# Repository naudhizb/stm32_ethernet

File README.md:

# stm32_ethernet
side project making stm32 ethernet module

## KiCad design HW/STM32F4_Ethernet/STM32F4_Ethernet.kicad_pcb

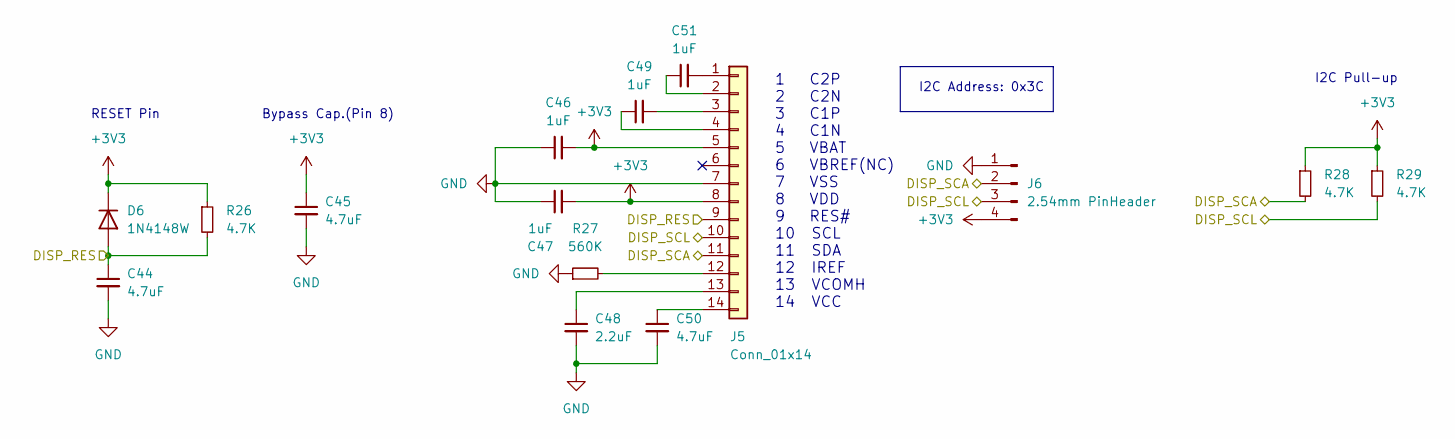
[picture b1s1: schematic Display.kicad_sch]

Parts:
C44, C45, C50: 4.7uF; C_0603_1608Metric_Pad1.08x0.95mm_HandSolder
C46, C47, C49, C51: 1uF; C_0603_1608Metric_Pad1.08x0.95mm_HandSolder
C48: 2.2uF; C_0603_1608Metric_Pad1.08x0.95mm_HandSolder
D6: 1N4148W; D_SOD-123
J5: Conn_01x14; OLED0_49
J6: 2.54mm PinHeader; PinHeader_1x04_P2.54mm_Vertical
R26, R28, R29: 4.7K; R_0603_1608Metric_Pad0.98x0.95mm_HandSolder
R27: 560K; R_0603_1608Metric_Pad0.98x0.95mm_HandSolder

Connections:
+3V3: C45.1, C46.2, C47.2, D6.1 (K), J5.5, J5.8, J6.4, R26.1, R28.1, R29.1; also elsewhere on the board
/Display/DISP_RES: C44.1, D6.2 (A), J5.9, R26.2
/Display/DISP_SCA: J5.11, J6.2, R28.2; also elsewhere on the board
/Display/DISP_SCL: J5.10, J6.3, R29.2; also elsewhere on the board
GND: C44.2, C45.2, C46.1, C47.1, C48.2, C50.2, J5.7, J6.1, R27.1; also elsewhere on the board
unnamed: C48.1, J5.13
unnamed: C49.1, J5.4
unnamed: C49.2, J5.3
unnamed: C50.1, J5.14
unnamed: C51.1, J5.2
unnamed: C51.2, J5.1
unnamed: J5.12, R27.2

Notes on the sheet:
1 C2P 2 C2N 3 C1P 4 C1N 5 VBAT 6 VBREF(NC) 7 VSS 8 VDD 9 RES# 10 SCL 11 SDA 12 IREF 13 VCOMH 14 VCC
I2C Pull-up
I2C Address: 0x3C
RESET Pin
Bypass Cap.(Pin 8)

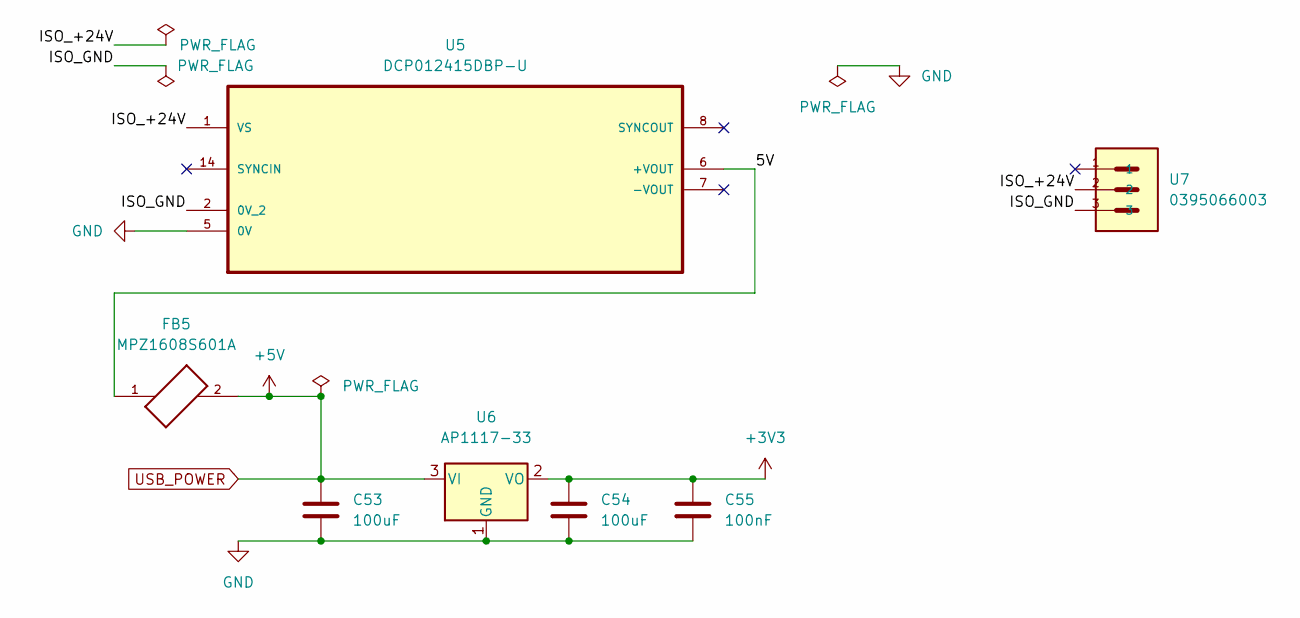
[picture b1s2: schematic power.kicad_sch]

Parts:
C53, C54: 100uF; C_0603_1608Metric_Pad1.08x0.95mm_HandSolder
C55: 100nF; C_0603_1608Metric_Pad1.08x0.95mm_HandSolder
FB5: MPZ1608S601A; BEADC1608X95N
U5: DCP012415DBP-U; SOP254P1050X533-14N; MPN DCP012415DBP-U
U6: AP1117-33; SOT-223-3_TabPin2
U7: 0395066003; MOLEX_0395066003

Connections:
+3V3: C54.1, C55.1, U6.2 (VO); also elsewhere on the board
/Power/5V: FB5.1, U5.6 (+VOUT)
/Power/ISO_+24V: U5.1 (VS), U7.2
/Power/ISO_GND: U5.2 (0V_2), U7.3
GND: C53.2, C54.2, C55.2, U5.5 (0V), U6.1 (GND); also elsewhere on the board
USB_POWER: C53.1, FB5.2, U6.3 (VI); also elsewhere on the board

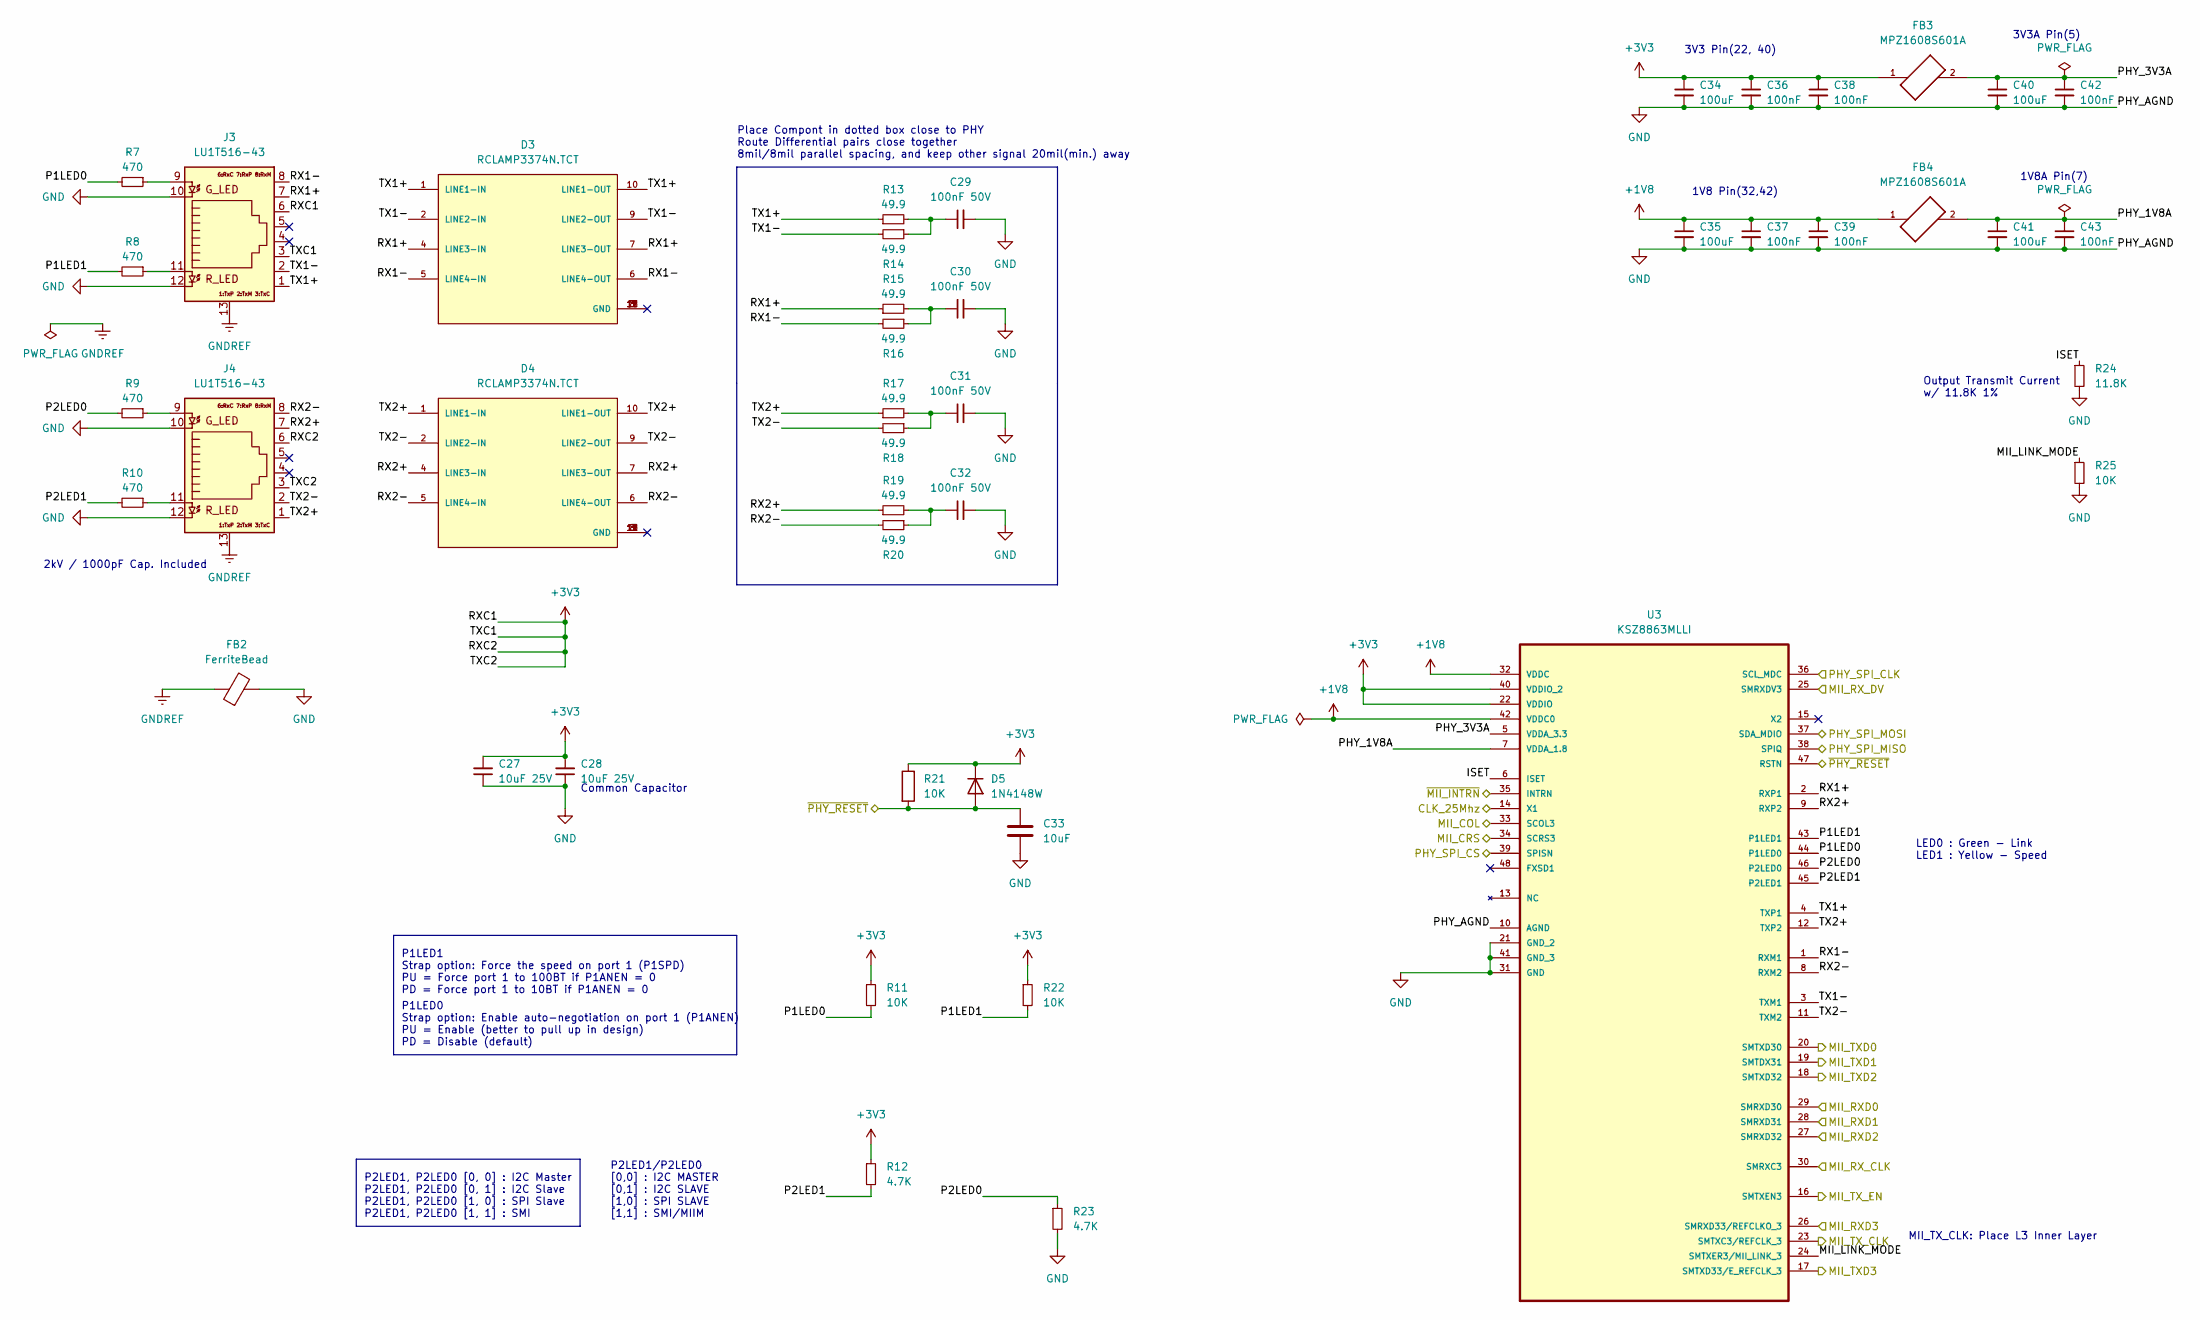
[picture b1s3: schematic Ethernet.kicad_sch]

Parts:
C27, C28: 10uF 25V; C_0603_1608Metric_Pad1.08x0.95mm_HandSolder
C29, C30, C31, C32: 100nF 50V; C_0603_1608Metric_Pad1.08x0.95mm_HandSolder
C33: 10uF; C_0603_1608Metric_Pad1.08x0.95mm_HandSolder
C34, C35, C40, C41: 100uF; C_0603_1608Metric_Pad1.08x0.95mm_HandSolder
C36, C37, C38, C39, C42, C43: 100nF; C_0603_1608Metric_Pad1.08x0.95mm_HandSolder
D3, D4: RCLAMP3374N.TCT; DIODE_RCLAMP3374N.TCT; PARTREV 7/24/2012
D5: 1N4148W; D_SOD-123
FB2: FerriteBead; BEADC1608X95N
FB3, FB4: MPZ1608S601A; BEADC1608X95N
J3, J4: LU1T516-43; LU1T516-43LF
R7, R8, R9, R10: 470; R_0603_1608Metric_Pad0.98x0.95mm_HandSolder
R11, R21, R22, R25: 10K; R_0603_1608Metric_Pad0.98x0.95mm_HandSolder
R12, R23: 4.7K; R_0603_1608Metric_Pad0.98x0.95mm_HandSolder
R13, R14, R15, R16, R17, R18, R19, R20: 49.9; R_0603_1608Metric_Pad0.98x0.95mm_HandSolder
R24: 11.8K; R_0603_1608Metric_Pad0.98x0.95mm_HandSolder
U3: KSZ8863MLLI; QFP50P900X900X160-48N; MPN KSZ8863MLLI

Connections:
+1V8: C35.1, C37.1, C39.1, FB4.1, U3.32 (VDDC), U3.42 (VDDC0)
+3V3: C27.2, C28.2, C34.1, C36.1, C38.1, D5.1 (K), FB3.1, J3.3, J3.6, J4.3, J4.6, R11.1, R12.1, R21.1, R22.1, U3.22 (VDDIO), U3.40 (VDDIO_2); also elsewhere on the board
/Ethernet/ISET: R24.1, U3.6 (ISET)
/Ethernet/MII_LINK_MODE: R25.1, U3.24 (SMTXER3/MII_LINK_3)
/Ethernet/P1LED0: R7.2, R11.2, U3.44 (P1LED0)
/Ethernet/P1LED1: R8.2, R22.2, U3.43 (P1LED1)
/Ethernet/P2LED0: R9.2, R23.1, U3.46 (P2LED0)
/Ethernet/P2LED1: R10.2, R12.2, U3.45 (P2LED1)
/Ethernet/PHY_1V8A: C41.1, C43.1, FB4.2, U3.7 (VDDA_1.8)
/Ethernet/PHY_3V3A: C40.1, C42.1, FB3.2, U3.5 (VDDA_3.3)
/Ethernet/RX1+: D3.4 (LINE3-IN), D3.7 (LINE3-OUT), J3.7, R15.1, U3.2 (RXP1)
/Ethernet/RX1-: D3.5 (LINE4-IN), D3.6 (LINE4-OUT), J3.8, R16.2, U3.1 (RXM1)
/Ethernet/RX2+: D4.4 (LINE3-IN), D4.7 (LINE3-OUT), J4.7, R19.1, U3.9 (RXP2)
/Ethernet/RX2-: D4.5 (LINE4-IN), D4.6 (LINE4-OUT), J4.8, R20.2, U3.8 (RXM2)
/Ethernet/TX1+: D3.1 (LINE1-IN), D3.10 (LINE1-OUT), J3.1, R13.1, U3.4 (TXP1)
/Ethernet/TX1-: D3.2 (LINE2-IN), D3.9 (LINE2-OUT), J3.2, R14.2, U3.3 (TXM1)
/Ethernet/TX2+: D4.1 (LINE1-IN), D4.10 (LINE1-OUT), J4.1, R17.1, U3.12 (TXP2)
/Ethernet/TX2-: D4.2 (LINE2-IN), D4.9 (LINE2-OUT), J4.2, R18.2, U3.11 (TXM2)
/MCU/ETH_COL: U3.33 (SCOL3); also elsewhere on the board
/MCU/ETH_CRS: U3.34 (SCRS3); also elsewhere on the board
/MCU/ETH_INT: U3.35 (INTRN); also elsewhere on the board
/MCU/ETH_RESET: C33.1, D5.2 (A), R21.2, U3.47 (RSTN); also elsewhere on the board
/MCU/ETH_RXD0: U3.29 (SMRXD30); also elsewhere on the board
/MCU/ETH_RXD1: U3.28 (SMRXD31); also elsewhere on the board
/MCU/ETH_RXD2: U3.27 (SMRXD32); also elsewhere on the board
/MCU/ETH_RXD3: U3.26 (SMRXD33/REFCLKO_3); also elsewhere on the board
/MCU/ETH_RX_CLK: U3.30 (SMRXC3); also elsewhere on the board
/MCU/ETH_RX_DV: U3.25 (SMRXDV3); also elsewhere on the board
/MCU/ETH_TXD0: U3.20 (SMTXD30); also elsewhere on the board
/MCU/ETH_TXD1: U3.19 (SMTDX31); also elsewhere on the board
/MCU/ETH_TXD2: U3.18 (SMTXD32); also elsewhere on the board
/MCU/ETH_TXD3: U3.17 (SMTXD33/E_REFCLK_3); also elsewhere on the board
/MCU/ETH_TX_CLK: U3.23 (SMTXC3/REFCLK_3); also elsewhere on the board
/MCU/ETH_TX_EN: U3.16 (SMTXEN3); also elsewhere on the board
/MCU/MCO_25MHz: U3.14 (X1); also elsewhere on the board
/MCU/SPI_MISO: U3.38 (SPIQ); also elsewhere on the board
/MCU/SPI_MOSI: U3.37 (SDA_MDIO); also elsewhere on the board
/MCU/SPI_NSS: U3.39 (SPISN); also elsewhere on the board
/MCU/SPI_SCK: U3.36 (SCL_MDC); also elsewhere on the board
GND: C27.1, C28.1, C29.2, C30.2, C31.2, C32.2, C33.2, C34.2, C35.2, C36.2, C37.2, C38.2, C39.2, C40.2, C41.2, C42.2, C43.2, FB2.2, J3.10, J3.12, J4.10, J4.12, R23.2, R24.2, R25.2, U3.10 (AGND), U3.21 (GND_2), U3.31 (GND), U3.41 (GND_3); also elsewhere on the board
GNDREF: FB2.1, J3.13, J4.13
unnamed: C29.1, R13.2, R14.1
unnamed: C30.1, R15.2, R16.1
unnamed: C31.1, R17.2, R18.1
unnamed: C32.1, R19.2, R20.1
unnamed: J3.9, R7.1
unnamed: J3.11, R8.1
unnamed: J4.9, R9.1
unnamed: J4.11, R10.1

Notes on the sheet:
P1LED1 Strap option: Force the speed on port 1 (P1SPD) PU = Force port 1 to 100BT if P1ANEN = 0 PD = Force port 1 to 10BT if P1ANEN = 0
1V8A Pin(7)
Output Transmit Current w/ 11.8K 1%
1V8 Pin(32,42)
Place Compont in dotted box close to PHY Route Differential pairs close together 8mil/8mil parallel spacing, and keep other signal 20mil(min.) away
P2LED1, P2LED0 [0, 0] : I2C Master P2LED1, P2LED0 [0, 1] : I2C Slave P2LED1, P2LED0 [1, 0] : SPI Slave P2LED1, P2LED0 [1, 1] : SMI
P1LED0 Strap option: Enable auto-negotiation on port 1 (P1ANEN) PU = Enable (better to pull up in design) PD = Disable (default)
MII_TX_CLK: Place L3 Inner Layer
Common Capacitor
3V3 Pin(22, 40)
2kV / 1000pF Cap. Included
LED0 : Green - Link LED1 : Yellow - Speed
3V3A Pin(5)
P2LED1/P2LED0 [0,0] : I2C MASTER [0,1] : I2C SLAVE [1,0] : SPI SLAVE [1,1] : SMI/MIIM

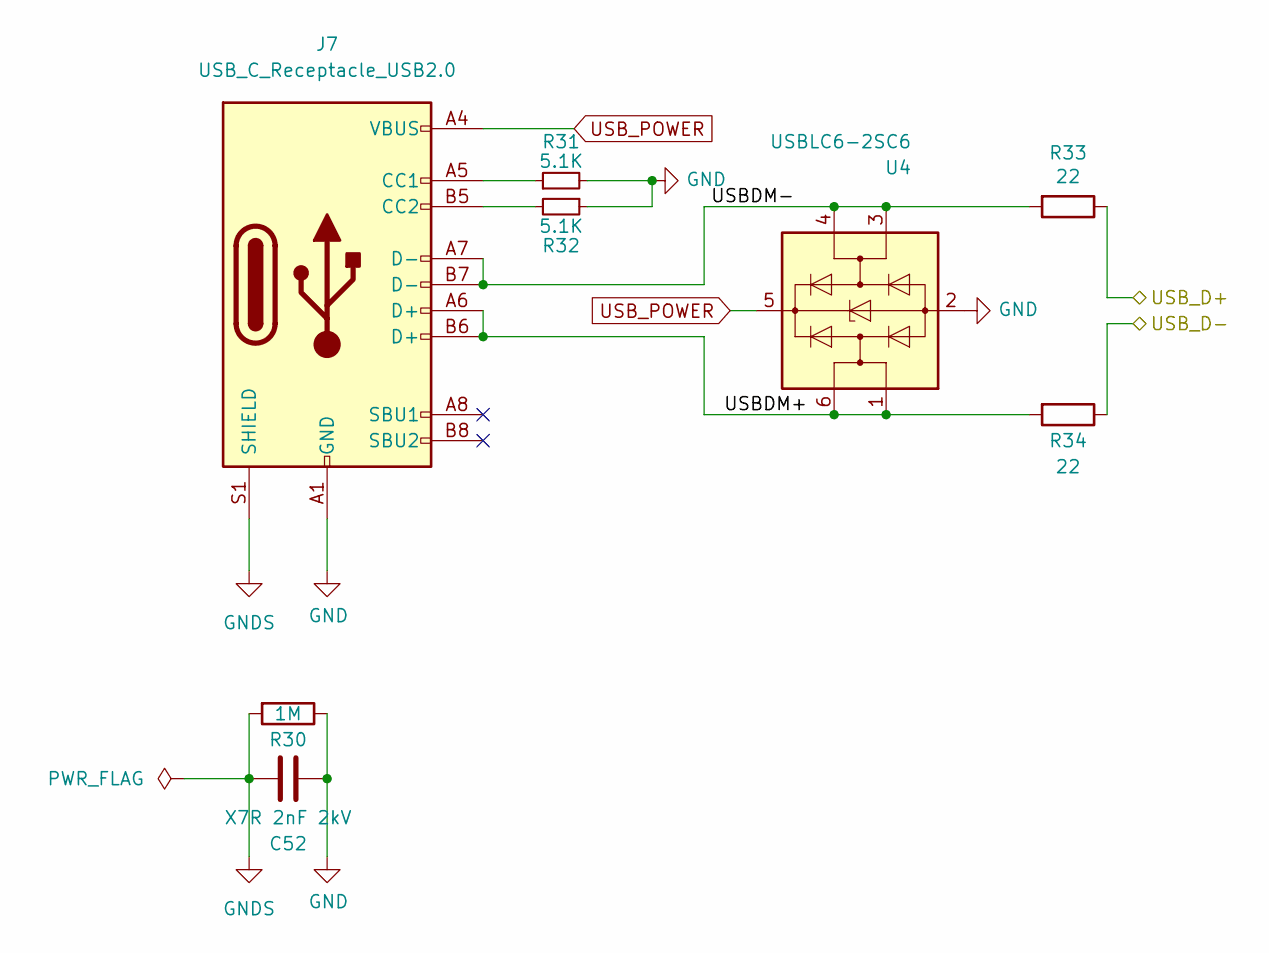
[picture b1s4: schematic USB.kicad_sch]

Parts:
C52: X7R 2nF 2kV; C_0603_1608Metric_Pad1.08x0.95mm_HandSolder
J7: USB_C_Receptacle_USB2.0; USB_C_Receptacle_Palconn_UTC16-G
R30: 1M; R_0603_1608Metric_Pad0.98x0.95mm_HandSolder
R31, R32: 5.1K; R_0603_1608Metric_Pad0.98x0.95mm_HandSolder
R33, R34: 22; R_0603_1608Metric_Pad0.98x0.95mm_HandSolder
U4: USBLC6-2SC6; SOT-23-6

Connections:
/MCU/USB_D+: R33.1; also elsewhere on the board
/MCU/USB_D-: R34.1; also elsewhere on the board
/USB/USBDM+: J7.A6 (D+), J7.B6 (D+), R34.2, U4.1 (I/O1), U4.6 (I/O1)
/USB/USBDM-: J7.A7 (D-), J7.B7 (D-), R33.2, U4.3 (I/O2), U4.4 (I/O2)
GND: C52.1, J7.A1 (GND), J7.A12 (GND), J7.B1 (GND), J7.B12 (GND), R30.1, R31.2, R32.1, U4.2 (GND); also elsewhere on the board
GNDS: C52.2, J7.S1 (SHIELD), R30.2
unnamed: J7.A5 (CC1), R31.1
unnamed: J7.B5 (CC2), R32.2
USB_POWER: J7.A4 (VBUS), J7.A9 (VBUS), J7.B4 (VBUS), J7.B9 (VBUS), U4.5 (VBUS); also elsewhere on the board

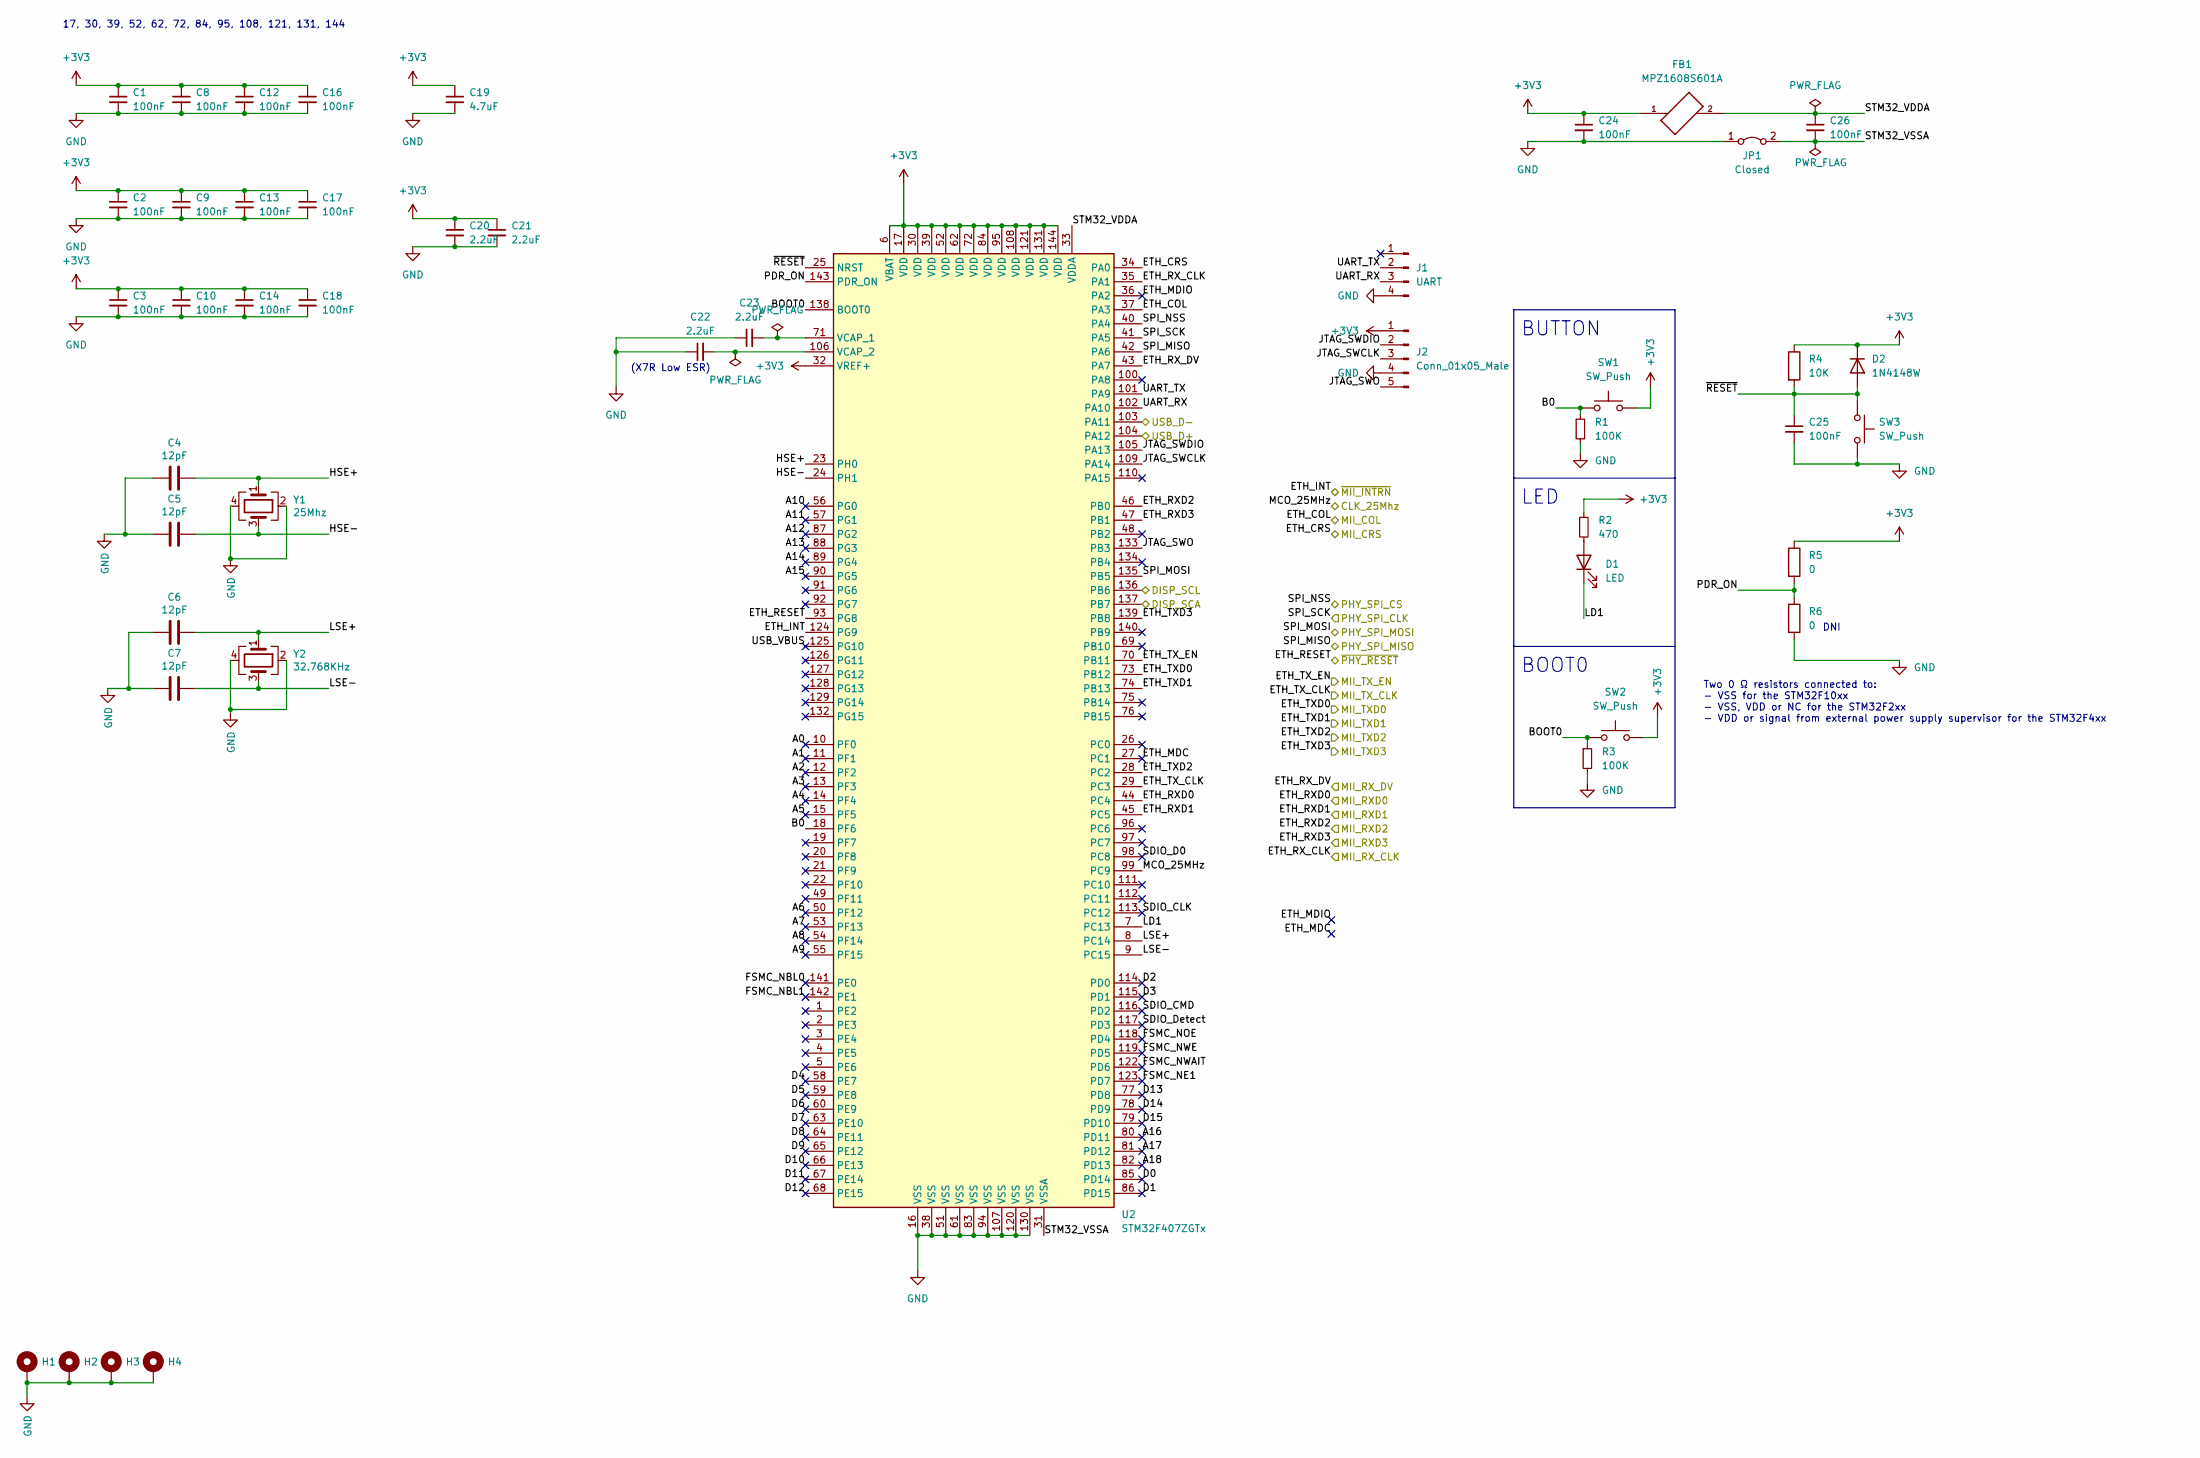
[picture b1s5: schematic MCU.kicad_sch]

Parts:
C1, C2, C3, C8, C9, C10, C12, C13, C14, C16, C17, C18, C24, C25, C26: 100nF; C_0603_1608Metric_Pad1.08x0.95mm_HandSolder
C4, C5, C6, C7: 12pF; C_0603_1608Metric_Pad1.08x0.95mm_HandSolder
C19: 4.7uF; C_0805_2012Metric_Pad1.18x1.45mm_HandSolder
C20, C21, C22, C23: 2.2uF; C_0805_2012Metric_Pad1.18x1.45mm_HandSolder
D1: LED; LED_0603_1608Metric_Pad1.05x0.95mm_HandSolder
D2: 1N4148W; D_SOD-123
FB1: MPZ1608S601A; BEADC1608X95N
H1, H2, H3, H4: MountingHole_3.2mm_M3_ISO7380_Pad
J1: UART; PinHeader_1x04_P2.54mm_Vertical
J2: Conn_01x05_Male; PinHeader_1x05_P2.54mm_Vertical
JP1: Closed; SolderJumper-2_P1.3mm_Open_TrianglePad1.0x1.5mm
R1, R3: 100K; R_0603_1608Metric_Pad0.98x0.95mm_HandSolder
R2: 470; R_0603_1608Metric_Pad0.98x0.95mm_HandSolder
R4: 10K; R_0603_1608Metric_Pad0.98x0.95mm_HandSolder
R5, R6: 0; R_0603_1608Metric_Pad0.98x0.95mm_HandSolder
SW1, SW2, SW3: SW_Push; SW_SPST_B3U-1000P-B
U2: STM32F407ZGTx; LQFP-144_20x20mm_P0.5mm
Y1: 25Mhz; Crystal_SMD_3225-4Pin_3.2x2.5mm_HandSoldering
Y2: 32.768KHz; Crystal_SMD_3225-4Pin_3.2x2.5mm_HandSoldering

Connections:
+3V3: C1.1, C2.1, C3.1, C8.1, C9.1, C10.1, C12.1, C13.1, C14.1, C16.1, C17.1, C18.1, C19.1, C20.1, C21.1, C24.1, D2.1 (K), FB1.1, J2.1, R2.1, R4.1, R5.1, SW1.2, SW2.2, U2.6 (VBAT), U2.17 (VDD), U2.30 (VDD), U2.32 (VREF+), U2.39 (VDD), U2.52 (VDD), U2.62 (VDD), U2.72 (VDD), U2.84 (VDD), U2.95 (VDD), U2.108 (VDD), U2.121 (VDD), U2.131 (VDD), U2.144 (VDD); also elsewhere on the board
/Display/DISP_SCA: U2.137 (PB7); also elsewhere on the board
/Display/DISP_SCL: U2.136 (PB6); also elsewhere on the board
/MCU/A0: U2.10 (PF0)
/MCU/A1: U2.11 (PF1)
/MCU/A2: U2.12 (PF2)
/MCU/A3: U2.13 (PF3)
/MCU/A4: U2.14 (PF4)
/MCU/A5: U2.15 (PF5)
/MCU/A6: U2.50 (PF12)
/MCU/A7: U2.53 (PF13)
/MCU/A8: U2.54 (PF14)
/MCU/A9: U2.55 (PF15)
/MCU/A10: U2.56 (PG0)
/MCU/A11: U2.57 (PG1)
/MCU/A12: U2.87 (PG2)
/MCU/A13: U2.88 (PG3)
/MCU/A14: U2.89 (PG4)
/MCU/A15: U2.90 (PG5)
/MCU/A16: U2.80 (PD11)
/MCU/A17: U2.81 (PD12)
/MCU/A18: U2.82 (PD13)
/MCU/B0: R1.1, SW1.1, U2.18 (PF6)
/MCU/BOOT0: R3.1, SW2.1, U2.138 (BOOT0)
/MCU/D0: U2.85 (PD14)
/MCU/D1: U2.86 (PD15)
/MCU/D2: U2.114 (PD0)
/MCU/D3: U2.115 (PD1)
/MCU/D4: U2.58 (PE7)
/MCU/D5: U2.59 (PE8)
/MCU/D6: U2.60 (PE9)
/MCU/D7: U2.63 (PE10)
/MCU/D8: U2.64 (PE11)
/MCU/D9: U2.65 (PE12)
/MCU/D10: U2.66 (PE13)
/MCU/D11: U2.67 (PE14)
/MCU/D12: U2.68 (PE15)
/MCU/D13: U2.77 (PD8)
/MCU/D14: U2.78 (PD9)
/MCU/D15: U2.79 (PD10)
/MCU/ETH_COL: U2.37 (PA3); also elsewhere on the board
/MCU/ETH_CRS: U2.34 (PA0); also elsewhere on the board
/MCU/ETH_INT: U2.124 (PG9); also elsewhere on the board
/MCU/ETH_MDC: U2.27 (PC1)
/MCU/ETH_MDIO: U2.36 (PA2)
/MCU/ETH_RESET: U2.93 (PG8); also elsewhere on the board
/MCU/ETH_RXD0: U2.44 (PC4); also elsewhere on the board
/MCU/ETH_RXD1: U2.45 (PC5); also elsewhere on the board
/MCU/ETH_RXD2: U2.46 (PB0); also elsewhere on the board
/MCU/ETH_RXD3: U2.47 (PB1); also elsewhere on the board
/MCU/ETH_RX_CLK: U2.35 (PA1); also elsewhere on the board
/MCU/ETH_RX_DV: U2.43 (PA7); also elsewhere on the board
/MCU/ETH_TXD0: U2.73 (PB12); also elsewhere on the board
/MCU/ETH_TXD1: U2.74 (PB13); also elsewhere on the board
/MCU/ETH_TXD2: U2.28 (PC2); also elsewhere on the board
/MCU/ETH_TXD3: U2.139 (PB8); also elsewhere on the board
/MCU/ETH_TX_CLK: U2.29 (PC3); also elsewhere on the board
/MCU/ETH_TX_EN: U2.70 (PB11); also elsewhere on the board
/MCU/FSMC_NBL0: U2.141 (PE0)
/MCU/FSMC_NBL1: U2.142 (PE1)
/MCU/FSMC_NE1: U2.123 (PD7)
/MCU/FSMC_NOE: U2.118 (PD4)
/MCU/FSMC_NWAIT: U2.122 (PD6)
/MCU/FSMC_NWE: U2.119 (PD5)
/MCU/HSE+: C4.1, U2.23 (PH0), Y1.1
/MCU/HSE-: C5.1, U2.24 (PH1), Y1.3
/MCU/JTAG_SWCLK: J2.3, U2.109 (PA14)
/MCU/JTAG_SWDIO: J2.2, U2.105 (PA13)
/MCU/JTAG_SWO: J2.5, U2.133 (PB3)
/MCU/LD1: D1.1 (K), U2.7 (PC13)
/MCU/LSE+: C6.1, U2.8 (PC14), Y2.1
/MCU/LSE-: C7.1, U2.9 (PC15), Y2.3
/MCU/MCO_25MHz: U2.99 (PC9); also elsewhere on the board
/MCU/PDR_ON: R5.2, R6.1, U2.143 (PDR_ON)
/MCU/SDIO_CLK: U2.113 (PC12)
/MCU/SDIO_CMD: U2.116 (PD2)
/MCU/SDIO_D0: U2.98 (PC8)
/MCU/SDIO_Detect: U2.117 (PD3)
/MCU/SPI_MISO: U2.42 (PA6); also elsewhere on the board
/MCU/SPI_MOSI: U2.135 (PB5); also elsewhere on the board
/MCU/SPI_NSS: U2.40 (PA4); also elsewhere on the board
/MCU/SPI_SCK: U2.41 (PA5); also elsewhere on the board
/MCU/STM32_VDDA: C26.1, FB1.2, U2.33 (VDDA)
/MCU/STM32_VSSA: C26.2, JP1.2 (B), U2.31 (VSSA)
/MCU/UART_RX: J1.3, U2.102 (PA10)
/MCU/UART_TX: J1.2, U2.101 (PA9)
/MCU/USB_D+: U2.104 (PA12); also elsewhere on the board
/MCU/USB_D-: U2.103 (PA11); also elsewhere on the board
/MCU/USB_VBUS: U2.125 (PG10)
/MCU/~RESET: C25.1, D2.2 (A), R4.2, SW3.1, U2.25 (NRST)
GND: C1.2, C2.2, C3.2, C4.2, C5.2, C6.2, C7.2, C8.2, C9.2, C10.2, C12.2, C13.2, C14.2, C16.2, C17.2, C18.2, C19.2, C20.2, C21.2, C22.1, C23.1, C24.2, C25.2, H1.1, H2.1, H3.1, H4.1, J1.4, J2.4, JP1.1 (A), R1.2, R3.2, R6.2, SW3.2, U2.16 (VSS), U2.38 (VSS), U2.51 (VSS), U2.61 (VSS), U2.83 (VSS), U2.94 (VSS), U2.107 (VSS), U2.120 (VSS), U2.130 (VSS), Y1.2, Y1.4, Y2.2, Y2.4; also elsewhere on the board
unnamed: C22.2, U2.106 (VCAP_2)
unnamed: C23.2, U2.71 (VCAP_1)
unnamed: D1.2 (A), R2.2

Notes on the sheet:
BUTTON
LED
DNI
BOOT0
17, 30, 39, 52, 62, 72, 84, 95, 108, 121, 131, 144
(X7R Low ESR)
Two 0 Ω resistors connected to: - VSS for the STM32F10xx - VSS, VDD or NC for the STM32F2xx - VDD or signal from external power supply supervisor for the STM32F4xx

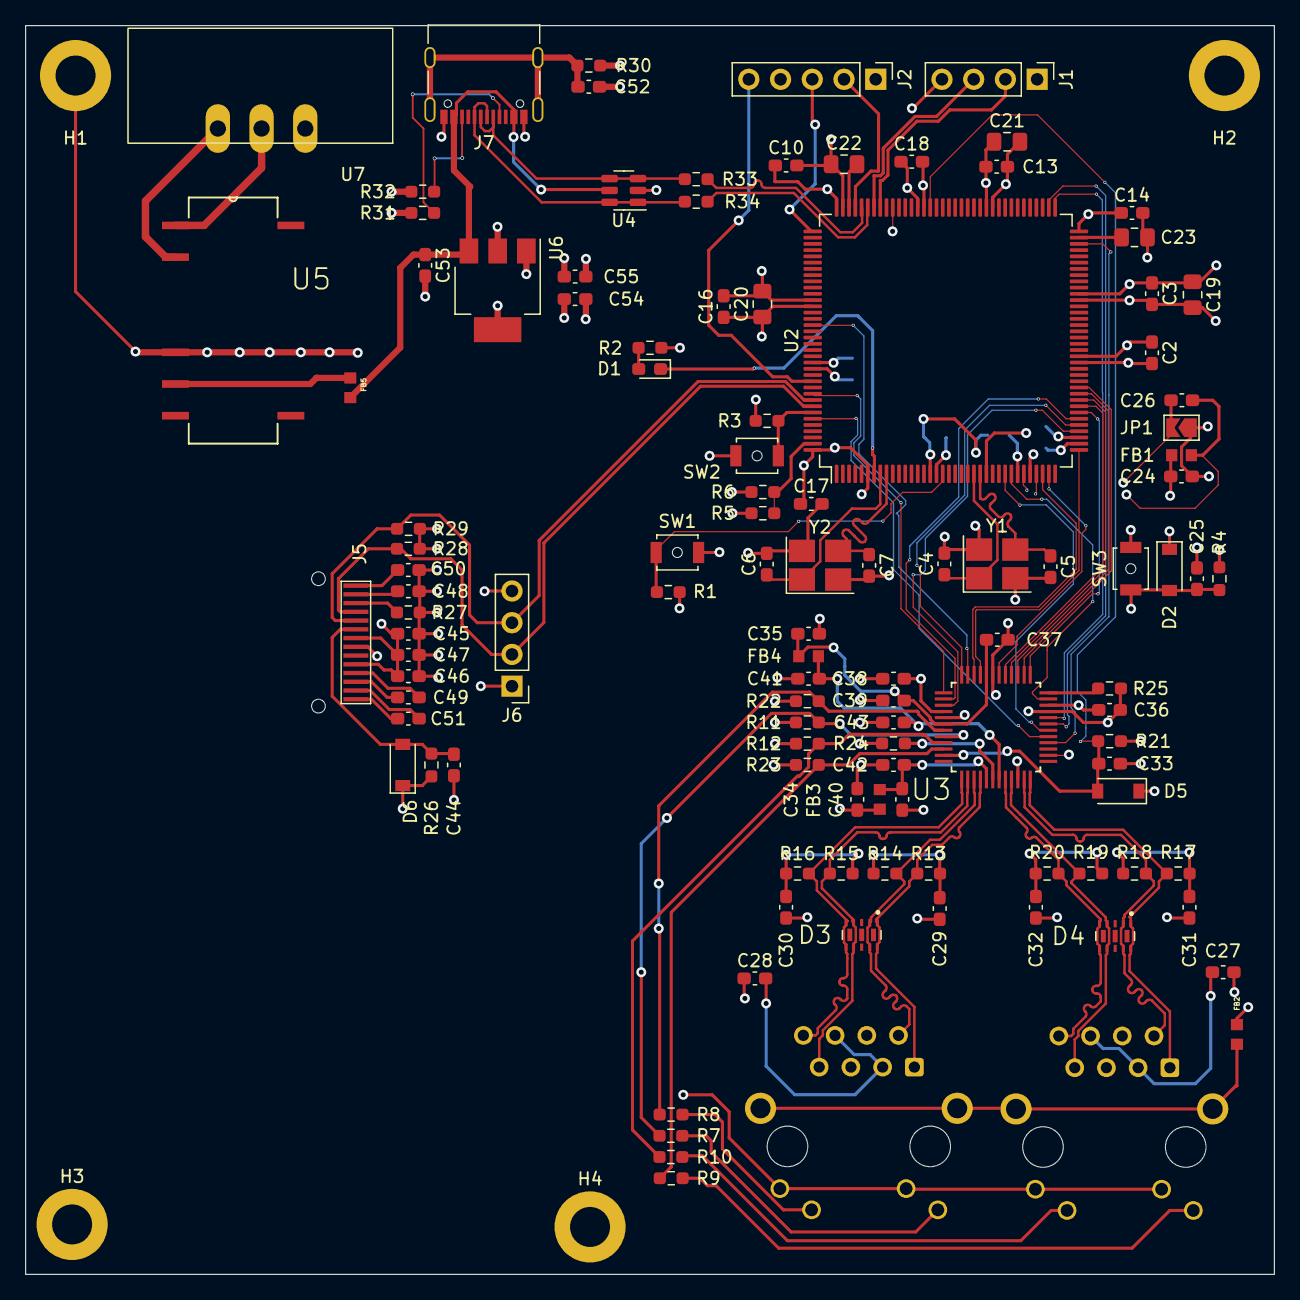
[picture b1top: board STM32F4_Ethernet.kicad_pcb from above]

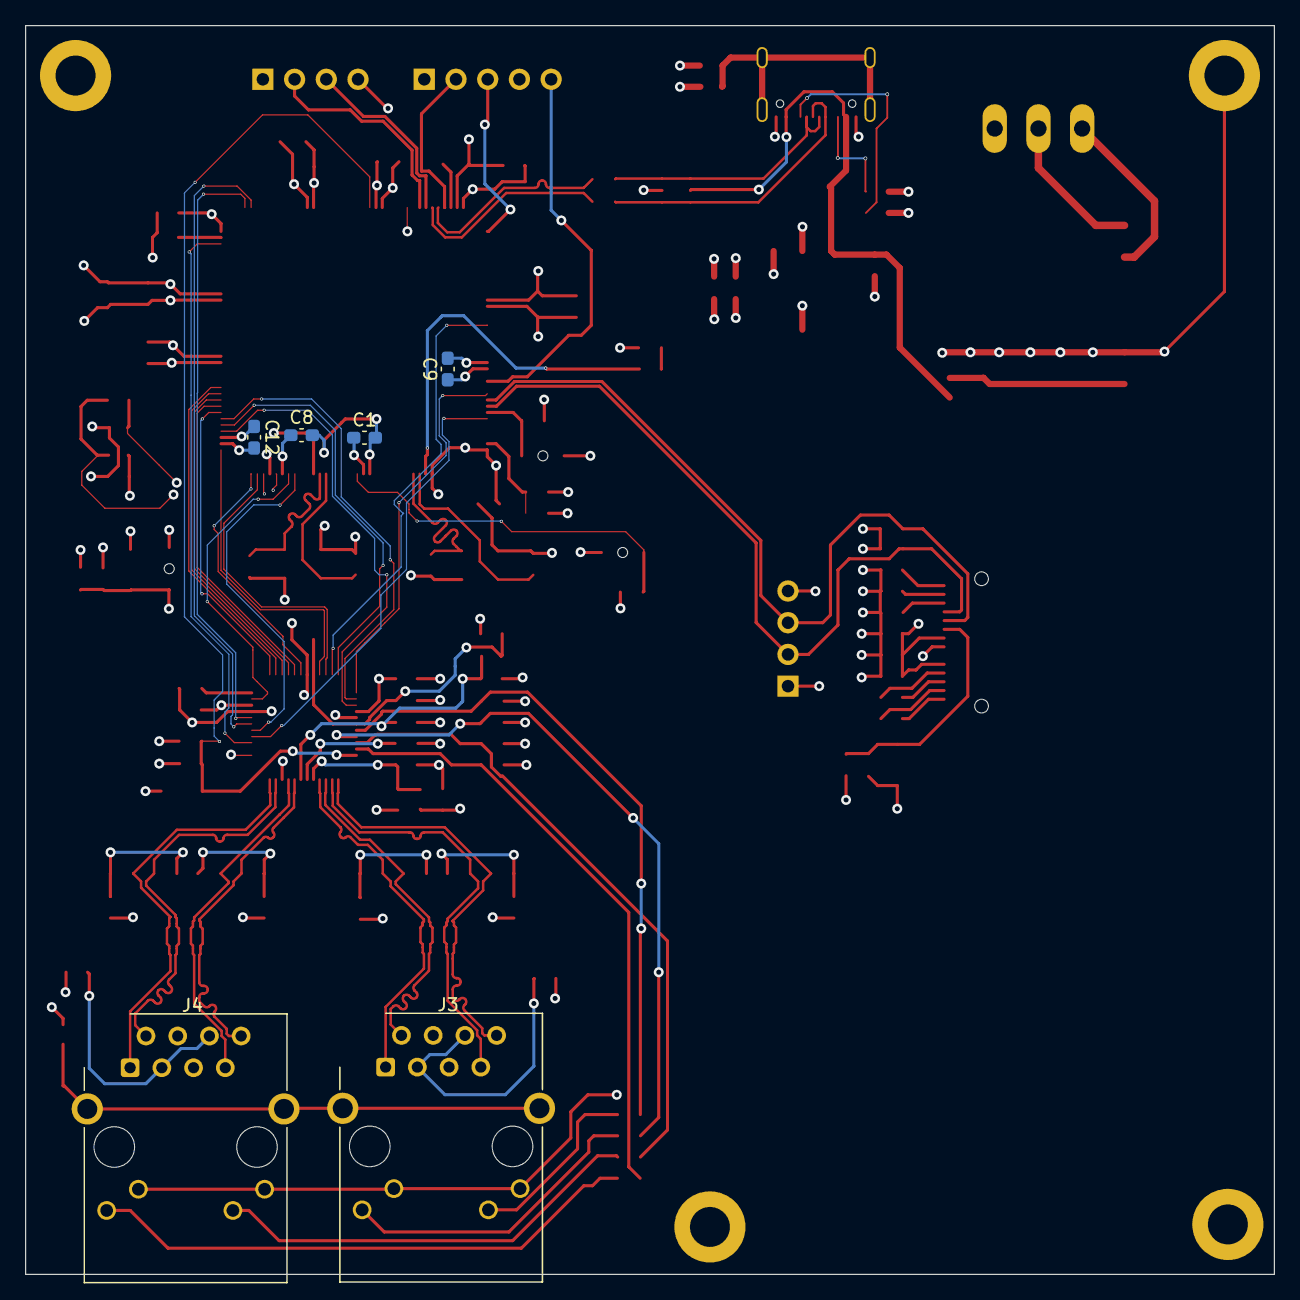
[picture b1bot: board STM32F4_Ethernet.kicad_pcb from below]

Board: 4 copper layers, 100.0 x 100.0 mm, 121 parts (6 on the bottom side), 89 nets.

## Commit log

2023-05-01 During development. add some library
2023-05-10 Progress backup
2023-05-15 Progress backup. add SRAM
2023-05-21 Sample PCB. Need to update RLC Size
